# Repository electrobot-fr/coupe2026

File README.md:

Coupe de France de Robotique Junior 2026

## Compilation

Chaque sous-dossier est un projet PlatformIO indépendant. Le `Makefile` à la racine fournit des raccourcis.

### Cartes standards

```bash
make base_roulante              # compiler
make upload-base_roulante       # compiler + flasher
make all                        # compiler toutes les cartes (sauf PAMI)
make clean                      # nettoyer toutes les cartes
```

Cartes disponibles : `base_roulante`, `carte_actionneurs`, `emetteur`, `recepteur`, `telecommande`.

### PAMI (5 variantes)

Le code du PAMI est commun mais le comportement est sélectionné à la compilation par le flag `-DPAMI_VARIANT=N`. Une cible Makefile existe par variante :

| Cible | Variante | Description |
|---|---|---|
| `make pami-ninja` | NINJA | Séquence longue avec accélérations/décélérations |
| `make pami-1` | PAMI1 | Séquence courte (2 virages) |
| `make pami-2` | PAMI2 | Délai 6s puis avance + virage |
| `make pami-3` | PAMI3 | Délai 3s puis longue avance |
| `make pami-4` | PAMI4 | Délai 8.5s puis ligne droite |

Pour flasher, préfixer par `upload-` :

```bash
make upload-pami-ninja
make upload-pami-1
# etc.
```

⚠️ Compiler directement avec `cd pami && pio run` échoue : `PAMI_VARIANT` n'est pas défini et le code lève un `#error`. Toujours passer par le Makefile.

### Décompte initial (DECOMPTE_INITIAL)

Chaque variante a une valeur de décompte par défaut (en secondes) :

| Variante | Décompte par défaut |
|---|---|
| `pami-ninja` | 5 s |
| `pami-1` … `pami-4` | 87 s |

Pour surcharger ponctuellement la valeur (sans modifier le code), passer `DECOMPTE=<secondes>` à `make` :

```bash
make pami-1 DECOMPTE=30           # compile pami-1 avec un décompte de 30 s
make upload-pami-ninja DECOMPTE=10 # flashe ninja avec un décompte de 10 s
```

La variable `DECOMPTE` n'est utilisée que si elle est définie ; sinon la valeur par défaut de la variante est utilisée.

### Ajouter une nouvelle variante de PAMI

1. Ajouter un `#define` dans `pami/src/main.cpp` (ex. `#define PAMI5 5`)
2. Ajouter le bloc `#if PAMI_VARIANT == PAMI5 ... #endif` avec la séquence
3. Ajouter la variante dans le `Makefile` :
   - Ajouter `5` à `PAMI_VARIANTS`
   - Ajouter `PAMI_FLAG_5 = 5`

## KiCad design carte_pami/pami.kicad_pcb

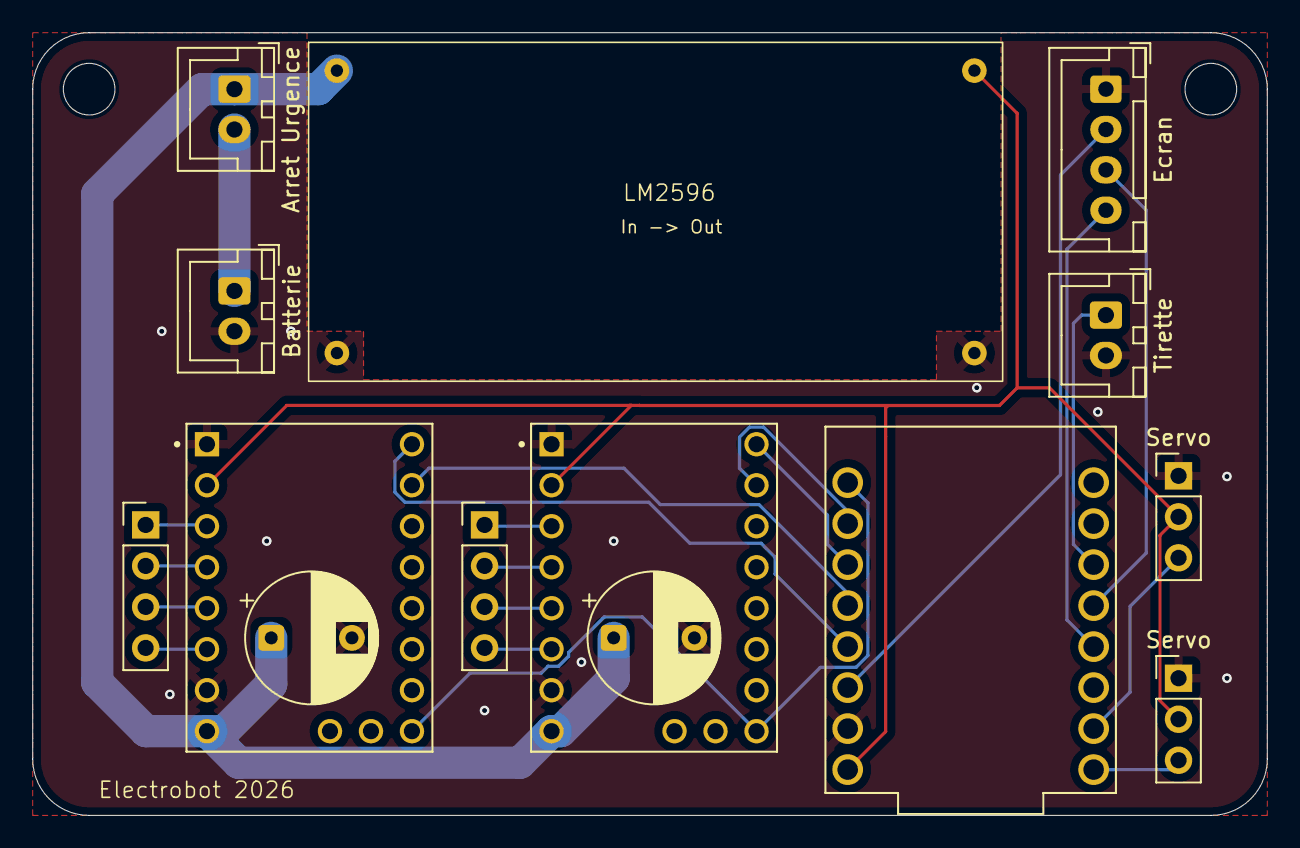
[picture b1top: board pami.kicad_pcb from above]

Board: 2 copper layers, 76.5 x 48.5 mm, 16 parts (0 on the bottom side), 23 nets.

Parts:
Arret Urgence: Arret urgence; JST_XH_B2B-XH-A_1x02_P2.50mm_Vertical
Batterie: LP E10 7.4V; JST_XH_B2B-XH-A_1x02_P2.50mm_Vertical
C1, C2: C_Polarized; CP_Radial_D8.0mm_P5.00mm
Ecran: Ecran OLED; JST_XH_B4B-XH-A_1x04_P2.50mm_Vertical
H1, H2: MountingHole; MountingHole_3.2mm_M3
J2: Moteur 1; PinHeader_1x04_P2.54mm_Vertical
J4: Moteur 2; PinHeader_1x04_P2.54mm_Vertical
Servo: Servo; PinHeader_1x03_P2.54mm_Vertical
Servo#2: Servo; PinHeader_1x03_P2.54mm_Vertical
Tirette: Tirette; JST_XH_B2B-XH-A_1x02_P2.50mm_Vertical
U1: ESP32-C3_SUPERMINI_TH; MODULE_ESP32-C3_SUPERMINI
U2: TMC2209 Moteur 1; MODULE_TMC2209_SILENTSTEPSTICK
U3: TMC2209 Moteur 2; MODULE_TMC2209_SILENTSTEPSTICK
VR1: Voltage Regulator; LM2596

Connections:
5V: Servo.2, Servo#2.2, U1.5V, U2.2 (VIO), U3.2 (VIO), VR1.4 (OUT+)
BAT: Arret Urgence.1, C1.1, C2.1, U2.8 (VM), U3.8 (VM), VR1.2 (IN+)
GND: Batterie.2, C1.2, C2.2, Ecran.1, Servo.1, Servo#2.1, Tirette.2, U1.G (GND), U2.1 (GND), U2.7 (GND), U3.1 (GND), U3.7 (GND), VR1.1 (IN-), VR1.3 (OUT-)
unnamed: Ecran.2, U1.3.3 (3V3)
unnamed: Ecran.3, U1.9 (GPIO9)
unnamed: Ecran.4, U1.8 (GPIO8)
unnamed: J2.1, U2.3 (M1B)
unnamed: J2.2, U2.4 (M1A)
unnamed: J2.3, U2.5 (M2A)
unnamed: J2.4, U2.6 (M2B)
unnamed: Arret Urgence.2, Batterie.1
unnamed: J4.1, U3.3 (M1B)
unnamed: J4.2, U3.4 (M1A)
unnamed: J4.3, U3.5 (M2A)
unnamed: J4.4, U3.6 (M2B)
unnamed: Tirette.1, U1.10 (GPIO10)
unnamed: Servo#2.3, U1.5 (GPIO5)
unnamed: Servo.3, U1.6 (GPIO6)
unnamed: U1.0 (GPIO0), U2.16 (~EN), U3.16 (~EN)
unnamed: U1.1 (GPIO1), U3.10 (STEP)
unnamed: U1.2 (GPIO2), U3.9 (DIR)
unnamed: U1.3 (GPIO3), U2.10 (STEP)
unnamed: U1.4 (GPIO4), U2.9 (DIR)

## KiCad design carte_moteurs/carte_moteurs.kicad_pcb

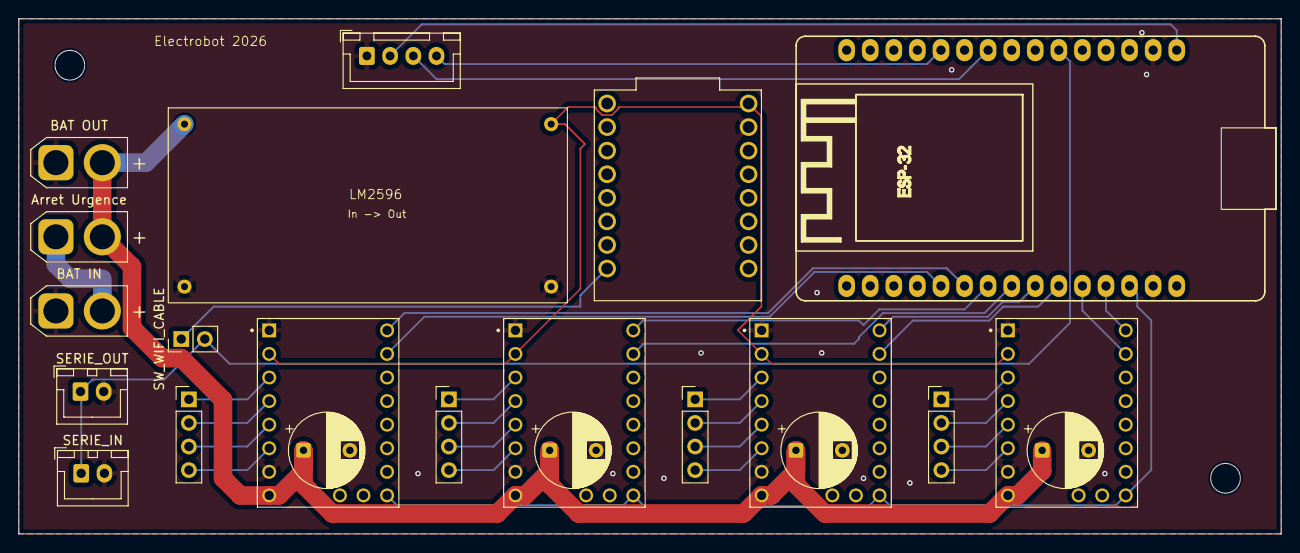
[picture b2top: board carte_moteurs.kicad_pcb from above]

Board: 2 copper layers, 136.0 x 55.5 mm, 24 parts (0 on the bottom side), 34 nets.

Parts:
A1: ESP32_DevKit_V1_DOIT_30GPIOs; DOIT_ESP32_DEVKIT_30Pins
Arret Urgence: Arret urgence; AMASS_XT30U-F_1x02_P5.0mm_Vertical
BAT IN: BAT_IN; AMASS_XT30U-F_1x02_P5.0mm_Vertical
BAT OUT: Conn_01x02_Socket; AMASS_XT30U-F_1x02_P5.0mm_Vertical
C1, C2, C3, C4: C_Polarized; CP_Radial_D8.0mm_P5.00mm
H1, H2: MountingHole; MountingHole_3.2mm_M3
J1: Ecran OLED; JST_XH_B4B-XH-A_1x04_P2.50mm_Vertical
J2: Moteur 1; PinHeader_1x04_P2.54mm_Vertical
J4: Moteur 2; PinHeader_1x04_P2.54mm_Vertical
J9: Moteur 4; PinHeader_1x04_P2.54mm_Vertical
J10: Moteur 3; PinHeader_1x04_P2.54mm_Vertical
SERIE_IN: Conn_01x02_Socket; JST_XH_B2B-XH-A_1x02_P2.50mm_Vertical
SERIE_OUT: Conn_01x02_Socket; JST_XH_B2B-XH-A_1x02_P2.50mm_Vertical
SW_WIFI_CABLE: Conn_01x02_Socket; PinHeader_1x02_P2.54mm_Vertical
U1: ESP32-C3_SUPERMINI_TH; MODULE_ESP32-C3_SUPERMINI
U2: TMC2209 Moteur 1; MODULE_TMC2209_SILENTSTEPSTICK
U3: TMC2209 Moteur 2; MODULE_TMC2209_SILENTSTEPSTICK
U4: TMC2209 Moteur 4; MODULE_TMC2209_SILENTSTEPSTICK
U5: TMC2209 Moteur 3; MODULE_TMC2209_SILENTSTEPSTICK
VR1: Voltage Regulator; LM2596

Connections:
5V: U1.5V, U2.2 (VIO), U3.2 (VIO), U4.2 (VIO), U5.2 (VIO), VR1.4 (OUT+)
/3V3: A1.1 (3.3V), J1.2
/DIR_M1: A1.21 (ADC1_CH4/D32), U2.9 (DIR)
/DIR_M2: A1.22 (ADC1_CH4/D32), U3.9 (DIR)
/DIR_M3: A1.27 (ADC2_CH5/D12), U5.9 (DIR)
/DIR_M4: A1.24 (DAC2/ADC2_CH9/D26), U4.9 (DIR)
/ESP_WIFI_TX: SW_WIFI_CABLE.1, U1.21 (GPIO21)
/OLED_SCK: A1.9 (D18), J1.3
/OLED_SDA: A1.11 (D21/SDA), J1.4
/STEP_M1: A1.20 (ADC1_CH7/D35), U2.10 (STEP)
/STEP_M2: A1.23 (DAC1/ADC2_CH8/D25), U3.10 (STEP)
/STEP_M3: A1.26 (ADC2_CH6/D14), U5.10 (STEP)
/STEP_M4: A1.25 (ADC2_CH7/D27), U4.10 (STEP)
/WROOM_RX: A1.6 (RX2/GPIO16), SERIE_IN.1, SERIE_OUT.1, SW_WIFI_CABLE.2
BAT: Arret Urgence.2, BAT OUT.2, C1.1, C2.1, C3.1, C4.1, U2.8 (VM), U3.8 (VM), U4.8 (VM), U5.8 (VM), VR1.2 (IN+)
EN: A1.28 (ADC2_CH4/D13), U2.16 (~EN), U3.16 (~EN), U4.16 (~EN), U5.16 (~EN)
GND: A1.2 (GND), A1.29 (GND), BAT IN.1, BAT OUT.1, C1.2, C2.2, C3.2, C4.2, J1.1, SERIE_IN.2, SERIE_OUT.2, U1.G (GND), U2.1 (GND), U2.7 (GND), U3.1 (GND), U3.7 (GND), U4.1 (GND), U4.7 (GND), U5.1 (GND), U5.7 (GND), VR1.1 (IN-), VR1.3 (OUT-)
unnamed: Arret Urgence.1, BAT IN.2
unnamed: J2.1, U2.3 (M1B)
unnamed: J2.2, U2.4 (M1A)
unnamed: J2.3, U2.5 (M2A)
unnamed: J2.4, U2.6 (M2B)
unnamed: J4.1, U3.3 (M1B)
unnamed: J4.2, U3.4 (M1A)
unnamed: J4.3, U3.5 (M2A)
unnamed: J4.4, U3.6 (M2B)
unnamed: J9.1, U4.3 (M1B)
unnamed: J9.2, U4.4 (M1A)
unnamed: J9.3, U4.5 (M2A)
unnamed: J9.4, U4.6 (M2B)
unnamed: J10.1, U5.3 (M1B)
unnamed: J10.2, U5.4 (M1A)
unnamed: J10.3, U5.5 (M2A)
unnamed: J10.4, U5.6 (M2B)

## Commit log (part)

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2025-09-27 Base PAMI
2025-09-27 Ajout base roulante
2025-09-27 Ajout du README
2025-09-27 Ligne droite
2025-10-05 Affichage PAMI
2025-10-09 Telecommande
2025-10-20 Translation
2025-11-08 ajout du pivot
2025-11-08 mise a jour de l'indentation
2025-11-08 correction translation
2025-11-10 Serial PAMI
2025-11-10 2 moteurs
2025-11-17 ajout servo et tirette
2025-11-22 tirette, déplacement des steppers en distance en mm et servomoteur à l afin du parcours
2025-11-30 ajout ecran oled et décompte
2025-12-23 Nouvelle carte
2025-12-23 LED status
2025-12-23 FastAccelStepper
2025-12-27 Commandes dans l'ordre
2025-12-27 Toutes les directions
2026-01-01 Ajout de l'ecureuil
2026-01-31 Sens
2026-02-14 V1 : prise en compte de tous les composants
2026-02-14 ajout affichage equipe J ou B
2026-03-13 Carte Actionneurs
2026-03-13 Claude
2026-03-14 Claude review
2026-03-14 Watchdog
2026-03-14 Simplification
2026-03-22 Ajout de l UI
2026-03-22 Strategie de base
2026-03-23 Seance de dimanche
2026-03-23 Timing pour les vannes
2026-03-23 Makefile
2026-03-24 Decoupage
2026-03-26 Boutons parfaits
2026-03-26 Affiche 2 nombres
2026-03-26 Selection quand on attrape
2026-03-26 Retournement
2026-03-27 Retourneurs
2026-03-29 boutons
2026-03-30 PAMI 1
2026-04-04 pami 2 3
2026-04-04 mise à jour du déplacement des 4 PAMI
2026-04-04 state
2026-04-04 Active le tapis
2026-04-04 State machine
2026-04-04 Simplify
2026-04-07 Delay
2026-04-10 pami
2026-04-18 PAMI Ninja
2026-04-22 Réglages des PAMI pour la coupe 2026
2026-05-10 ninja
2026-05-11 Réglages PAMI 1 à 4
2026-05-13 decalage
2026-05-14 jaune
2026-05-14 make pami
2026-05-14 fusion
